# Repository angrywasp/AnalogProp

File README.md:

# AnalogProp
A Simple P8X32A propeller development board with AD7812 ADC

## Requirements

You will also need a couple of tool, which can be imnstalled from Nuget.  
- proptool, a basic command line tool for flashing the firmware and serial monitoring. Compatible with the AnalogProp or any propeller compatible USB-UART device such as the PropPlug  
- bsi, the BasicScript interpreter. BasicScript is a simple, cross platform interpreter scripting language that is used

dotnet tool install -g AngryWasp.PropTool AngryWasp.BasicScript.Interpreter  
dotnet tool install -g AngryWasp.BasicScript.Interpreter

You can find out more about these tools and download the source from their respective repos:  
BasicScript: https://github.com/AngryWasp/AngryWasp.BasicScript    
PropTool: https://github.com/AngryWasp/AngryWasp.PropTool  

## Compiling the example

Simplest is to just run 'helloWorld.bs'. This script calls make.bs to build and then install the helloWorld program   

```powershell
bsi ./helloWorld.bs
```

For complete control over the install, you can use proptool directly. run 'proptool --help' for a full list of available command line options

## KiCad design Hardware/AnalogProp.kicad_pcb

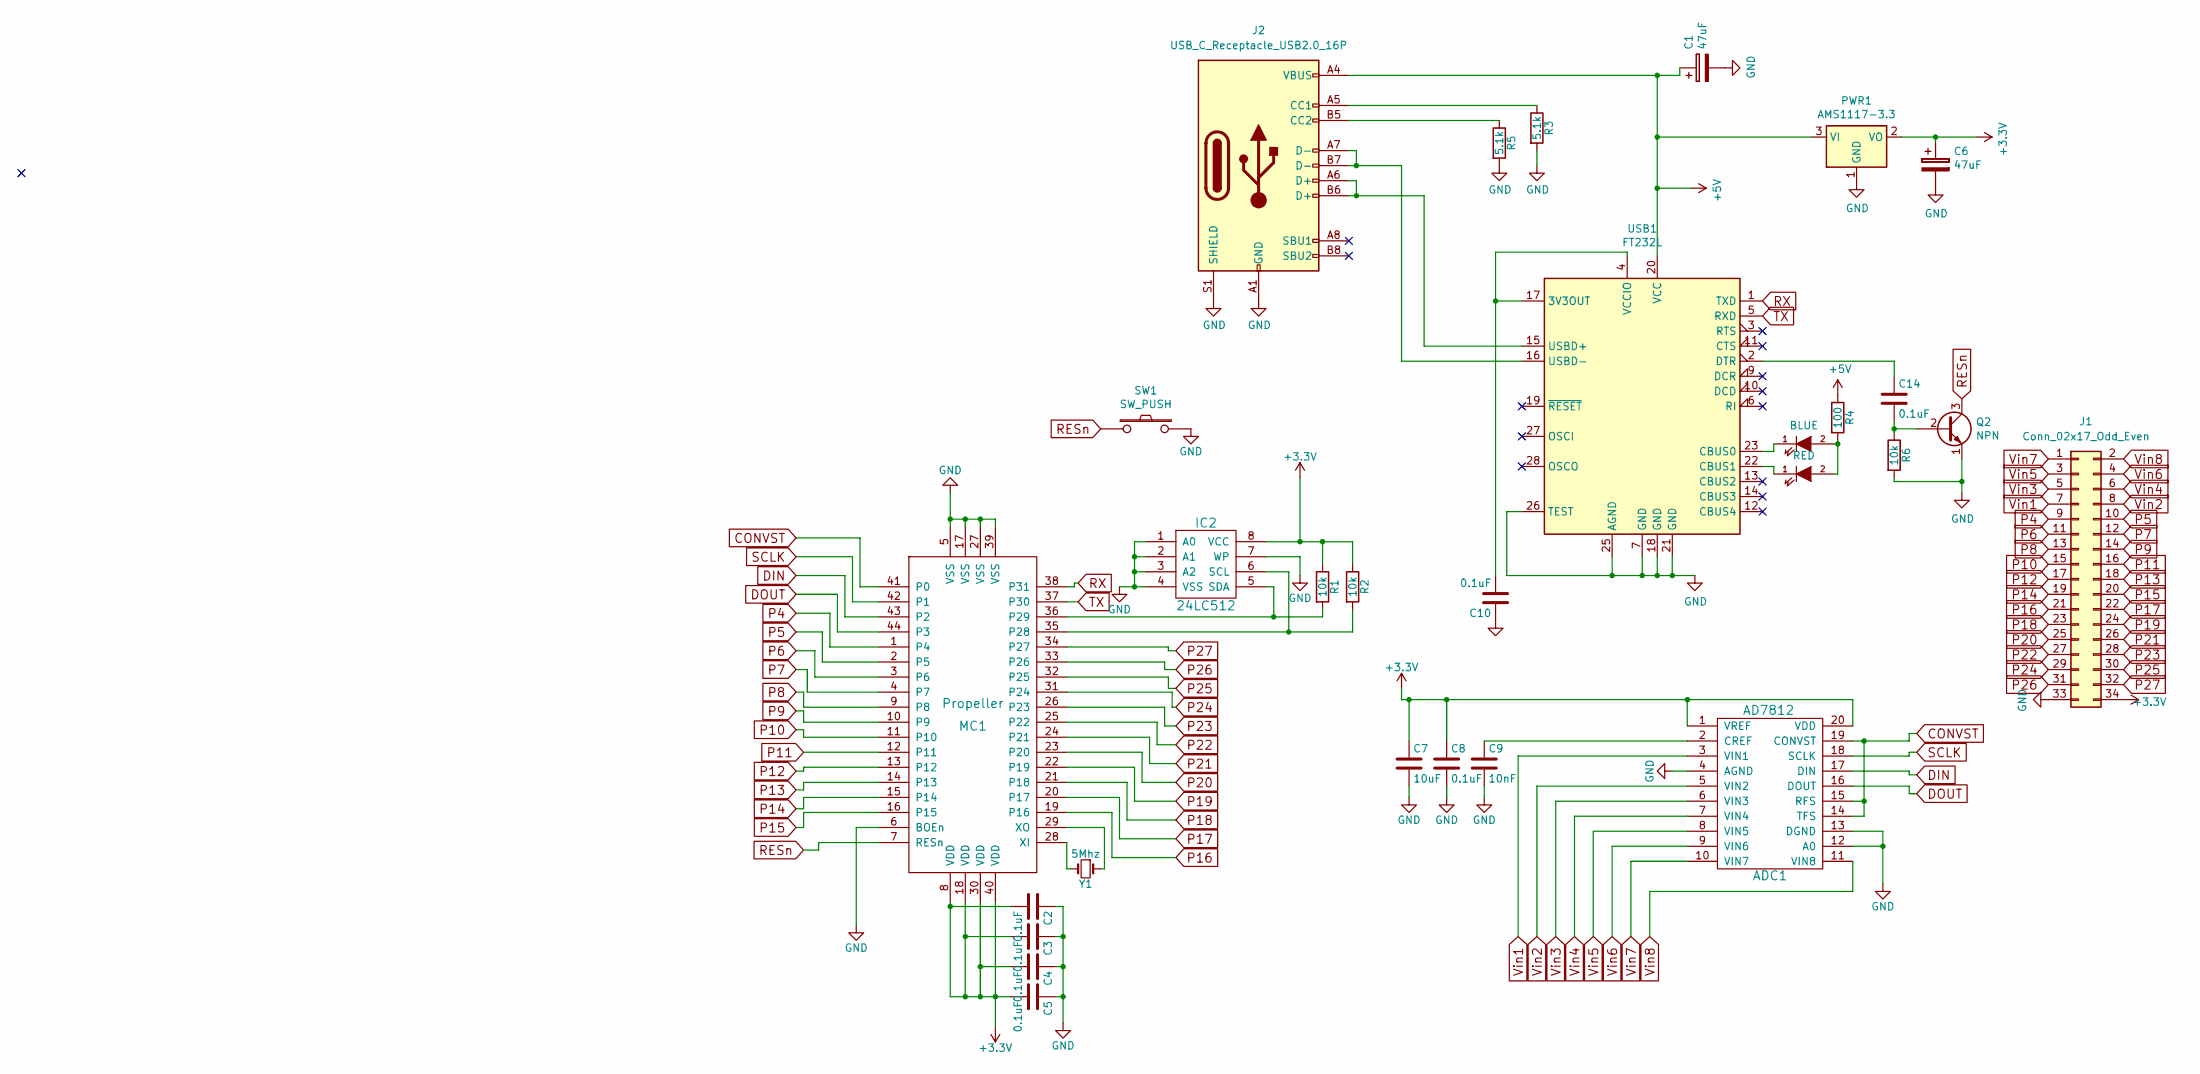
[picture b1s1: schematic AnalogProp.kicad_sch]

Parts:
ADC1: AD7812
C1, C6: 47uF; CP_Elec_5x5.4
C2, C3, C4, C5, C8, C10, C14: 0.1uF; 0805_HS
C7: 10uF; 0805_HS
C9: 10nF; 0805_HS
D2: BLUE; LED_0805_HS
D3: RED; LED_0805_HS
IC2: 24LC512; 24LC512-W
J1: Conn_02x17_Odd_Even; PinHeader_2x17_P2.54mm_Vertical
J2: USB_C_Receptacle_USB2.0_16P; USB_C_Receptacle_G-Switch_GT-USB-7010ASV
MC1: Propeller; P8X32A
PWR1: AMS1117-3.3; SOT-223
Q2: NPN; SOT-23_HS
R1, R2, R6: 10k; 0805_HS
R3, R5: 5.1k; 0805_HS
R4: 100; 0805_HS
SW1: SW_PUSH; SW_SPST
USB1: FT232L; SSOP-28_5.3x10.2mm_P0.65mm
Y1: 5Mhz; XTAL-2

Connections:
+3.3V: ADC1.1 (VREF), ADC1.20 (VDD), C2.2, C3.2, C4.2, C5.2, C6.1, C7.1, C8.1, IC2.8 (VCC), J1.34, MC1.8 (VDD), MC1.18 (VDD), MC1.30 (VDD), MC1.40 (VDD), PWR1.2 (VO), R1.1, R2.1
+5V: C1.1, J2.A4 (VBUS), J2.A9 (VBUS), J2.B4 (VBUS), J2.B9 (VBUS), PWR1.3 (VI), R4.1, USB1.20 (VCC)
CONVST: ADC1.14 (TFS), ADC1.15 (RFS), ADC1.19 (CONVST), MC1.41 (P0)
DIN: ADC1.17 (DIN), MC1.43 (P2)
DOUT: ADC1.16 (DOUT), MC1.44 (P3)
GND: ADC1.4 (AGND), ADC1.12 (A0), ADC1.13 (DGND), C1.2, C2.1, C3.1, C4.1, C5.1, C6.2, C7.2, C8.2, C9.2, C10.1, IC2.1 (A0), IC2.2 (A1), IC2.3 (A2), IC2.4 (VSS), IC2.7 (WP), J1.33, J2.A1 (GND), J2.A12 (GND), J2.B1 (GND), J2.B12 (GND), J2.S1 (SHIELD), MC1.5 (VSS), MC1.6 (BOEn), MC1.17 (VSS), MC1.27 (VSS), MC1.39 (VSS), PWR1.1 (GND), Q2.1 (E), R3.2, R5.2, R6.2, SW1.2, USB1.7 (GND), USB1.18 (GND), USB1.21 (GND), USB1.25 (AGND), USB1.26 (TEST)
unnamed: ADC1.2 (CREF), C9.1
unnamed: D2.2 (A), D3.2 (A), R4.2
unnamed: D2.1 (K), USB1.23 (CBUS0)
unnamed: D3.1 (K), USB1.22 (CBUS1)
unnamed: IC2.6 (SCL), MC1.35 (P28), R2.2
unnamed: IC2.5 (SDA), MC1.36 (P29), R1.2
unnamed: J2.A5 (CC1), R3.1
unnamed: J2.B5 (CC2), R5.1
unnamed: MC1.28 (XI), Y1.2
unnamed: MC1.29 (XO), Y1.1
unnamed: C14.2, Q2.2 (B), R6.1
unnamed: C10.2, USB1.4 (VCCIO), USB1.17 (3V3OUT)
unnamed: C14.1, USB1.2 (DTR)
unnamed: J2.A6 (D+), J2.B6 (D+), USB1.15 (USBD+)
unnamed: J2.A7 (D-), J2.B7 (D-), USB1.16 (USBD-)
P4: J1.9, MC1.1 (P4)
P5: J1.10, MC1.2 (P5)
P6: J1.11, MC1.3 (P6)
P7: J1.12, MC1.4 (P7)
P8: J1.13, MC1.9 (P8)
P9: J1.14, MC1.10 (P9)
P10: J1.15, MC1.11 (P10)
P11: J1.16, MC1.12 (P11)
P12: J1.17, MC1.13 (P12)
P13: J1.18, MC1.14 (P13)
P14: J1.19, MC1.15 (P14)
P15: J1.20, MC1.16 (P15)
P16: J1.21, MC1.19 (P16)
P17: J1.22, MC1.20 (P17)
P18: J1.23, MC1.21 (P18)
P19: J1.24, MC1.22 (P19)
P20: J1.25, MC1.23 (P20)
P21: J1.26, MC1.24 (P21)
P22: J1.27, MC1.25 (P22)
P23: J1.28, MC1.26 (P23)
P24: J1.29, MC1.31 (P24)
P25: J1.30, MC1.32 (P25)
P26: J1.31, MC1.33 (P26)
P27: J1.32, MC1.34 (P27)
RESn: MC1.7 (RESn), Q2.3 (C), SW1.1
RX: MC1.38 (P31), USB1.1 (TXD)
SCLK: ADC1.18 (SCLK), MC1.42 (P1)
TX: MC1.37 (P30), USB1.5 (RXD)
Vin1: ADC1.3 (VIN1), J1.7
Vin2: ADC1.5 (VIN2), J1.8
Vin3: ADC1.6 (VIN3), J1.5
Vin4: ADC1.7 (VIN4), J1.6
Vin5: ADC1.8 (VIN5), J1.3
Vin6: ADC1.9 (VIN6), J1.4
Vin7: ADC1.10 (VIN7), J1.1
Vin8: ADC1.11 (VIN8), J1.2

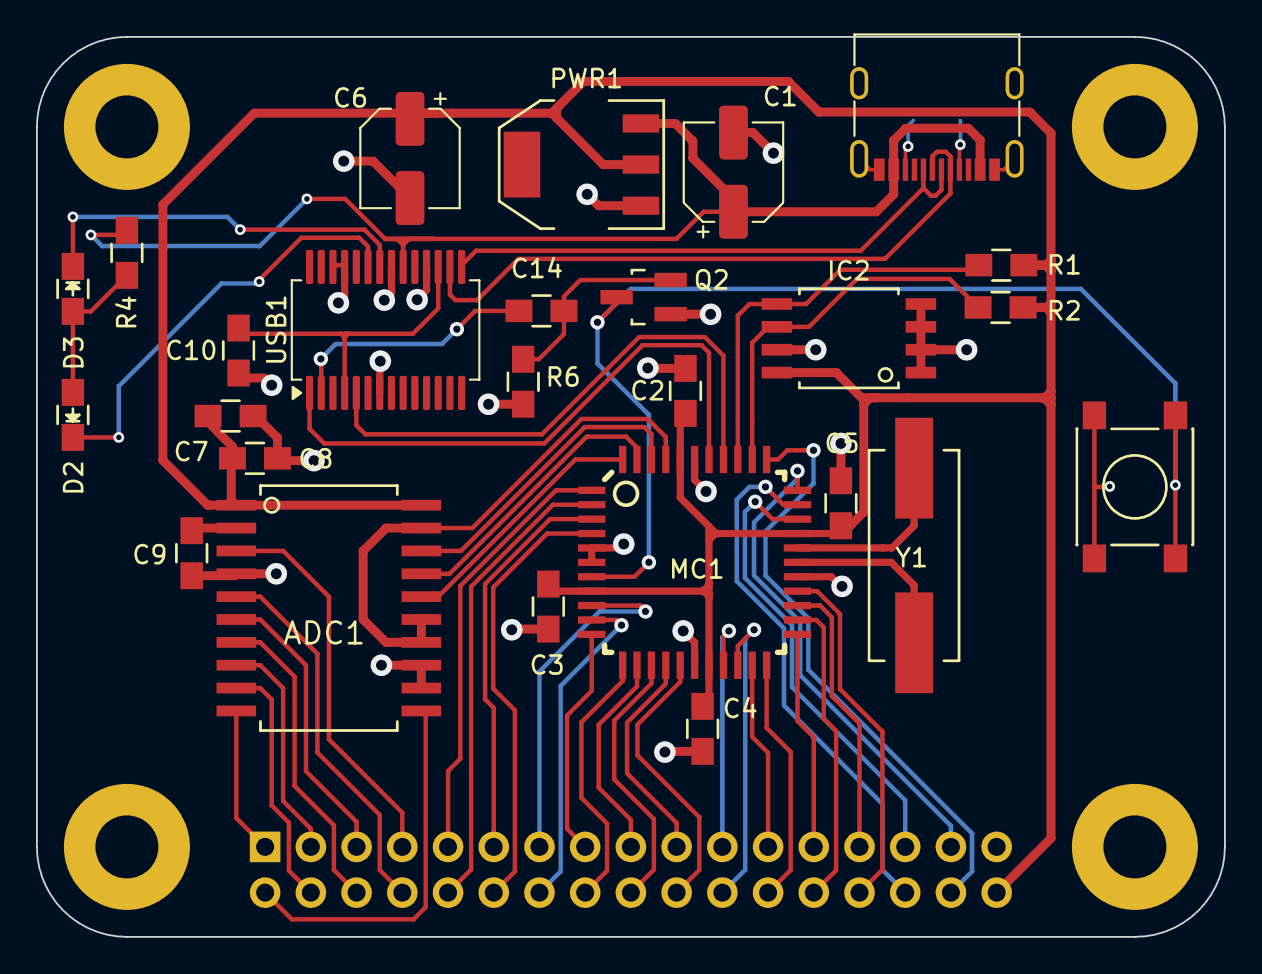
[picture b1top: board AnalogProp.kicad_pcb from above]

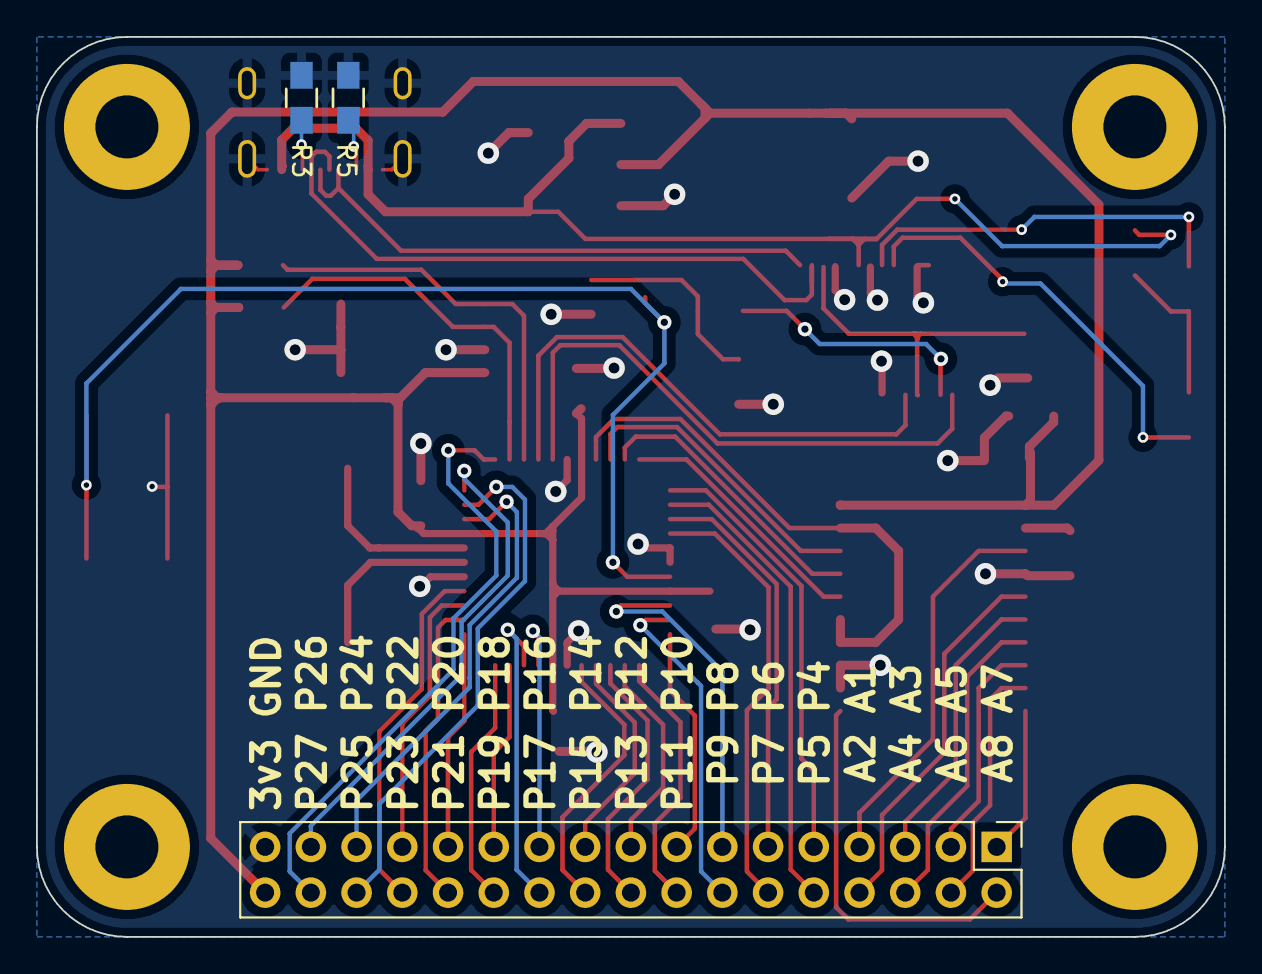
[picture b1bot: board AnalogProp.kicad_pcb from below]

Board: 2 copper layers, 66.0 x 50.0 mm, 29 parts (3 on the bottom side), 57 nets.

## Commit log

2026-05-19 Simplify build and update readme
2026-05-19 Remove GCC as a submodule
